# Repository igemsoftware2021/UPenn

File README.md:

# UPenn

OptoReader repository for software package to run the OptoReader, hardware files, and modeling scripts.

## Running the OptoReader

The OptoReader can be run using a computer and two Arduino Micros with the following provided code files: 

*OptoPlate_topArduino.ino* - Arduino code to control the stimulation plate. Takes in experiment stimulation settings, controls the 96 stimulation and optical density LEDs, and communicates with the reading plate for optical density measurements.

*PlateReader_bottomArduino.ino* - Arduino code to control the reading plate. Takes in experiment reading settings, controls the 96 excitation LEDs and photosensors, and communicates with the stimulation plate for optical density measurements. 

*OptoReader_Protocol.py* - Python code to take in inputs from the graphical user interface, keep track of experiment timing, and communicate with Arduinos to initiate readings and calibrate the optical density LEDs.

*GUI.py* - Python code creating a graphical user interface to take in user experiment inputs including stimulation settings, reading settings, feedback control, and experiment timing.

To run the OptoReader, first upload OptoPlate_topArduino.ino to the stimulation (top) plate Arduino and upload *PlateReader_bottomArduino.ino* to the reading (bottom) Arduino. Note the port name for each Arduino. If necessary, rename the port name from the preset COM11 and COM12 in *OptoReader_Protocol.py*. Finally, run GUI.py to open the graphical user interface and enter your experiment settings. Ensure that the image files *blue_logo.png* and *optologo_small.png* and the Python file *OptoReader_Protocol.py* are saved in the same folder as *GUI.py*.

## Hardware

### 3D Printed Parts
Includes files for our 3D-printed parts *Bottom_Adaptor.stl* and *Top_Adaptor.stl*. These files include the 3D model of the top adaptor and bottom adaptor, that fit each pcb board to a microwell plate.

### PCBs
Includes schematic files for our printed circuit boards (PCBs) *PlateReader.kicad_pcb* and *optoPlate96.kicad_pcb*. These can be sent directly to a company that provides printed circuit boards. The board components are soldered directly onto the boards. 

## Fluorescence Calibration Modeling

Files for our fluorescence calibration modeling include *FirstFit.m* and *Fluorescence_Calibration_Curve.m*. These files use our device’s fluorescence readings at different known concentrations to fit each well to a fluorescent calibration curve.

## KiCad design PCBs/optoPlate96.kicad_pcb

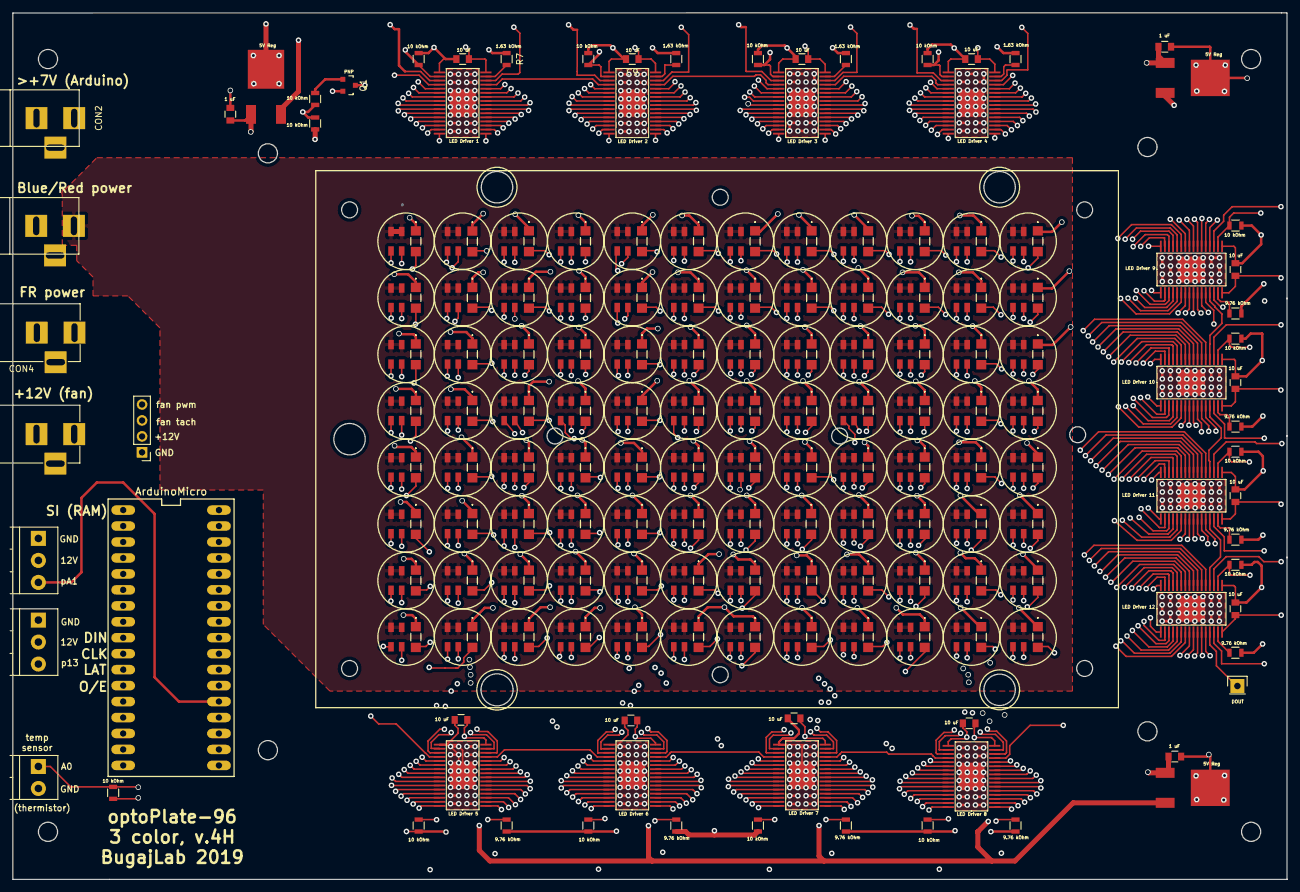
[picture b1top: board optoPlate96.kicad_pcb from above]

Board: 6 copper layers, 202.8 x 137.9 mm, 260 parts (0 on the bottom side), 332 nets.

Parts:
C7, C8, C9, C10, C11, C12, C13, C14, C15, C16, C17, C18, C19, C25, C27: C; C_0805
CON1, CON2, CON3, CON4: BARREL_JACK
D3, D5, D7, D9, D11, D13, D15, D17, D19, D21, D23, D25, D27, D29, D31, D33, D35, D37, D39, D41, D43, D45, D47, D49, D51, D53, D55, D57, D59, D61, D63, D65, D67, D69, D71, D73, D75, D77, D79, D81, D83, D85, D87, D89, D91, D93, D95, D97, D99, D101, D103, D105, D107, D109, D111, D113, D115, D117, D119, D121, D123, D125, D127, D129, D131, D133, D135, D137, D139, D141, D143, D145, D147, D149, D151, D153, D155, D157, D159, D161, D163, D165, D167, D169, D171, D173, D175, D177, D179, D181, D183, D185, D187, D189, D191, D193: LED; HSMCC380
D4, D6, D8, D10, D12, D14, D16, D18, D20, D22, D24, D26, D28, D30, D32, D34, D36, D38, D40, D42, D44, D46, D48, D50, D52, D54, D56, D58, D60, D62, D64, D66, D68, D70, D72, D74, D76, D78, D80, D82, D84, D86, D88, D90, D92, D94, D96, D98, D100, D102, D104, D106, D108, D110, D112, D114, D116, D118, D120, D122, D124, D126, D128, D130, D132, D134, D136, D138, D140, D142, D144, D146, D148, D150, D152, D154, D156, D158, D160, D162, D164, D166, D168, D170, D172, D174, D176, D178, D180, D182, D184, D186, D188, D190, D192, D194: BI_LED; BiLED3528RedBlue
P2: CONN_01X01; Pin_Header_Straight_1x01
P3, P6: CONN_01X03; TerminalBlock_Pheonix_PT-3.5mm_3pol
P4: CONN_01X04; Pin_Header_Straight_1x04_Pitch2.54mm
P5: CONN_01X02; TerminalBlock_Pheonix_PT-3.5mm_2pol
Q1: PNP; PNP_SOT-23_correct
R1, R2, R3, R6, R7, R8, R9, R10, R11, R12, R13, R14, R15, R16, R17, R18, R19, R20, R21, R22, R23, R24, R25, R26, R27, R28, R29: R; R_0805
U1: ArduinoMicro; ArduinoMicro_DIP34
U4, U17, U18: LM2931AZ-5.0; Voltage_Regulator_LM2931ADT-5.0_noHoles
U5, U6, U7, U8, U9, U10, U11, U12, U13, U14, U15, U16: TLC5947; TLC5947_noHoles

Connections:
/3.3V: CON1.1, D4.1, D4.2, D6.1, D6.2, D8.1, D8.2, D10.1, D10.2, D12.1, D12.2, D14.1, D14.2, D16.1, D16.2, D18.1, D18.2, D20.1, D20.2, D22.1, D22.2, D24.1, D24.2, D26.1, D26.2, D28.1, D28.2, D30.1, D30.2, D32.1, D32.2, D34.1, D34.2, D36.1, D36.2, D38.1, D38.2, D40.1, D40.2, D42.1, D42.2, D44.1, D44.2, D46.1, D46.2, D48.1, D48.2, D50.1, D50.2, D52.1, D52.2, D54.1, D54.2, D56.1, D56.2, D58.1, D58.2, D60.1, D60.2, D62.1, D62.2, D64.1, D64.2, D66.1, D66.2, D68.1, D68.2, D70.1, D70.2, D72.1, D72.2, D74.1, D74.2, D76.1, D76.2, D78.1, D78.2, D80.1, D80.2, D82.1, D82.2, D84.1, D84.2, D86.1, D86.2, D88.1, D88.2, D90.1, D90.2, D92.1, D92.2, D94.1, D94.2, D96.1, D96.2, D98.1, D98.2, D100.1, D100.2, D102.1, D102.2, D104.1, D104.2, D106.1, D106.2, D108.1, D108.2, D110.1, D110.2, D112.1, D112.2, D114.1, D114.2, D116.1, D116.2, D118.1, D118.2, D120.1, D120.2, D122.1, D122.2, D124.1, D124.2, D126.1, D126.2, D128.1, D128.2, D130.1, D130.2, D132.1, D132.2, D134.1, D134.2, D136.1, D136.2, D138.1, D138.2, D140.1, D140.2, D142.1, D142.2, D144.1, D144.2, D146.1, D146.2, D148.1, D148.2, D150.1, D150.2, D152.1, D152.2, D154.1, D154.2, D156.1, D156.2, D158.1, D158.2, D160.1, D160.2, D162.1, D162.2, D164.1, D164.2, D166.1, D166.2, D168.1, D168.2, D170.1, D170.2, D172.1, D172.2, D174.1, D174.2, D176.1, D176.2, D178.1, D178.2, D180.1, D180.2, D182.1, D182.2, D184.1, D184.2, D186.1, D186.2, D188.1, D188.2, D190.1, D190.2, D192.1, D192.2, D194.1, D194.2
/3.3Vreal: R3.2, U1.19, U1.20
/5V: C13.1, C25.1, C27.1, CON2.1, U1.32, U4.3, U17.3, U18.3
/+12V: CON3.1, P3.2, P4.2, P6.2
/B1: D4.4, U5.5
/B2: D6.4, U5.6
/B3: D8.4, U5.7
/B4: D10.4, U5.8
/B5: D12.4, U5.9
/B6: D14.4, U5.10
/B7: D16.4, U5.11
/B8: D18.4, U5.12
/B9: D20.4, U5.13
/B10: D22.4, U5.14
/B11: D24.4, U5.15
/B12: D26.4, U5.16
/B13: D28.4, U5.17
/B14: D30.4, U5.18
/B15: D32.4, U5.19
/B16: D34.4, U5.20
/B17: D36.4, U5.21
/B18: D38.4, U5.22
/B19: D40.4, U5.23
/B20: D42.4, U5.24
/B21: D44.4, U5.25
/B22: D46.4, U5.26
/B23: D48.4, U5.27
/B24: D50.4, U5.28
/B25: D52.4, U6.5
/B26: D54.4, U6.6
/B27: D56.4, U6.7
/B28: D58.4, U6.8
/B29: D60.4, U6.9
/B30: D62.4, U6.10
/B31: D64.4, U6.11
/B32: D66.4, U6.12
/B33: D68.4, U6.13
/B34: D70.4, U6.14
/B35: D72.4, U6.15
/B36: D74.4, U6.16
/B37: D76.4, U6.17
/B38: D78.4, U6.18
/B39: D80.4, U6.19
/B40: D82.4, U6.20
/B41: D84.4, U6.21
/B42: D86.4, U6.22
/B43: D88.4, U6.23
/B44: D90.4, U6.24
/B45: D92.4, U6.25
/B46: D94.4, U6.26
/B47: D96.4, U6.27
/B48: D98.4, U6.28
/B49: D100.4, U7.5
/B50: D102.4, U7.6
/B51: D104.4, U7.7
/B52: D106.4, U7.8
/B53: D108.4, U7.9
/B54: D110.4, U7.10
/B55: D112.4, U7.11
/B56: D114.4, U7.12
/B57: D116.4, U7.13
/B58: D118.4, U7.14
/B59: D120.4, U7.15
/B60: D122.4, U7.16
/B61: D124.4, U7.17
/B62: D126.4, U7.18
/B63: D128.4, U7.19
/B64: D130.4, U7.20
/B65: D132.4, U7.21
/B66: D134.4, U7.22
/B67: D136.4, U7.23
/B68: D138.4, U7.24
/B69: D140.4, U7.25
/B70: D142.4, U7.26
/B71: D144.4, U7.27
/B72: D146.4, U7.28
/B73: D148.4, U8.5
/B74: D150.4, U8.6
/B75: D152.4, U8.7
/B76: D154.4, U8.8
/B77: D156.4, U8.9
/B78: D158.4, U8.10
/B79: D160.4, U8.11
/B80: D162.4, U8.12
/B81: D164.4, U8.13
/B82: D166.4, U8.14
/B83: D168.4, U8.15
/B84: D170.4, U8.16
/B85: D172.4, U8.17
/B86: D174.4, U8.18
/B87: D176.4, U8.19
/B88: D178.4, U8.20
/B89: D180.4, U8.21
/B90: D182.4, U8.22
/B91: D184.4, U8.23
/B92: D186.4, U8.24
/B93: D188.4, U8.25
/B94: D190.4, U8.26
/B95: D192.4, U8.27
/B96: D194.4, U8.28
/BLANK: Q1.3, R6.2, R8.2, R10.2, R12.2, R14.2, R16.2, R18.2, R20.2, R22.2, R24.2, R26.2, R28.2, U5.2, U6.2, U7.2, U8.2, U9.2, U10.2, U11.2, U12.2, U13.2, U14.2, U15.2, U16.2
/CLK: U1.10, U5.3, U6.3, U7.3, U8.3, U9.3, U10.3, U11.3, U12.3, U13.3, U14.3, U15.3, U16.3
/DIN: U1.9, U5.4
/DOUT: P2.1, U16.29
/FR1: D3.2, U13.5
/FR2: D5.2, U13.17
/FR3: D7.2, U14.5
/FR4: D9.2, U14.17
/FR5: D11.2, U15.5
/FR6: D13.2, U15.17
/FR7: D15.2, U16.5
/FR8: D17.2, U16.17
/FR9: D19.2, U13.6
/FR10: D21.2, U13.18
/FR11: D23.2, U14.6
/FR12: D25.2, U14.18
/FR13: D27.2, U15.6
/FR14: D29.2, U15.18
/FR15: D31.2, U16.6
/FR16: D33.2, U16.18
/FR17: D35.2, U13.7
/FR18: D37.2, U13.19
/FR19: D39.2, U14.7
/FR20: D41.2, U14.19
/FR21: D43.2, U15.7
/FR22: D45.2, U15.19
/FR23: D47.2, U16.7
/FR24: D49.2, U16.19
/FR25: D51.2, U13.8
/FR26: D53.2, U13.20
/FR27: D55.2, U14.8
/FR28: D57.2, U14.20
/FR29: D59.2, U15.8
/FR30: D61.2, U15.20
/FR31: D63.2, U16.8
/FR32: D65.2, U16.20
/FR33: D67.2, U13.9
/FR34: D69.2, U13.21
/FR35: D71.2, U14.9
/FR36: D73.2, U14.21
/FR37: D75.2, U15.9
/FR38: D77.2, U15.21
/FR39: D79.2, U16.9
/FR40: D81.2, U16.21
/FR41: D83.2, U13.10
/FR42: D85.2, U13.22
/FR43: D87.2, U14.10
/FR44: D89.2, U14.22
/FR45: D91.2, U15.10
/FR46: D93.2, U15.22
/FR47: D95.2, U16.10
/FR48: D97.2, U16.22
/FR49: D99.2, U13.11
/FR50: D101.2, U13.23
/FR51: D103.2, U14.11
/FR52: D105.2, U14.23
/FR53: D107.2, U15.11
/FR54: D109.2, U15.23
/FR55: D111.2, U16.11
/FR56: D113.2, U16.23
/FR57: D115.2, U13.12
/FR58: D117.2, U13.24
/FR59: D119.2, U14.12
/FR60: D121.2, U14.24
/FR61: D123.2, U15.12
/FR62: D125.2, U15.24
/FR63: D127.2, U16.12
/FR64: D129.2, U16.24
/FR65: D131.2, U13.13
/FR66: D133.2, U13.25
/FR67: D135.2, U14.13
/FR68: D137.2, U14.25
/FR69: D139.2, U15.13
/FR70: D141.2, U15.25
/FR71: D143.2, U16.13
/FR72: D145.2, U16.25
/FR73: D147.2, U13.14
/FR74: D149.2, U13.26
/FR75: D151.2, U14.14
/FR76: D153.2, U14.26
/FR77: D155.2, U15.14
/FR78: D157.2, U15.26
/FR79: D159.2, U16.14
/FR80: D161.2, U16.26
/FR81: D163.2, U13.15
/FR82: D165.2, U13.27
/FR83: D167.2, U14.15
/FR84: D169.2, U14.27
/FR85: D171.2, U15.15
/FR86: D173.2, U15.27
/FR87: D175.2, U16.15
/FR88: D177.2, U16.27
/FR89: D179.2, U13.16
/FR90: D181.2, U13.28
/FR91: D183.2, U14.16
/FR92: D185.2, U14.28
/FR93: D187.2, U15.16
/FR94: D189.2, U15.28
/FR95: D191.2, U16.16
/FR96: D193.2, U16.28
/LAT: U1.11, U5.30, U6.30, U7.30, U8.30, U9.30, U10.30, U11.30, U12.30, U13.30, U14.30, U15.30, U16.30
/R1: D4.3, U9.5
/R2: D6.3, U9.6
/R3: D8.3, U9.7
/R4: D10.3, U9.8
/R5: D12.3, U9.9
/R6: D14.3, U9.10
/R7: D16.3, U9.11
/R8: D18.3, U9.12
/R9: D20.3, U9.13
/R10: D22.3, U9.14
/R11: D24.3, U9.15
/R12: D26.3, U9.16
/R13: D28.3, U9.17
/R14: D30.3, U9.18
/R15: D32.3, U9.19
/R16: D34.3, U9.20
/R17: D36.3, U9.21
/R18: D38.3, U9.22
/R19: D40.3, U9.23
/R20: D42.3, U9.24
/R21: D44.3, U9.25
/R22: D46.3, U9.26
/R23: D48.3, U9.27
/R24: D50.3, U9.28
/R25: D52.3, U10.5
/R26: D54.3, U10.6
/R27: D56.3, U10.7
/R28: D58.3, U10.8
/R29: D60.3, U10.9
/R30: D62.3, U10.10
/R31: D64.3, U10.11
/R32: D66.3, U10.12
/R33: D68.3, U10.13
/R34: D70.3, U10.14
/R35: D72.3, U10.15
/R36: D74.3, U10.16
/R37: D76.3, U10.17
/R38: D78.3, U10.18
/R39: D80.3, U10.19
/R40: D82.3, U10.20
/R41: D84.3, U10.21
/R42: D86.3, U10.22
/R43: D88.3, U10.23
/R44: D90.3, U10.24
/R45: D92.3, U10.25
/R46: D94.3, U10.26
/R47: D96.3, U10.27
/R48: D98.3, U10.28
/R49: D100.3, U11.5
/R50: D102.3, U11.6
/R51: D104.3, U11.7
/R52: D106.3, U11.8
/R53: D108.3, U11.9
/R54: D110.3, U11.10
/R55: D112.3, U11.11
/R56: D114.3, U11.12
/R57: D116.3, U11.13
/R58: D118.3, U11.14
/R59: D120.3, U11.15
/R60: D122.3, U11.16
/R61: D124.3, U11.17
/R62: D126.3, U11.18
/R63: D128.3, U11.19
/R64: D130.3, U11.20
/R65: D132.3, U11.21
/R66: D134.3, U11.22
/R67: D136.3, U11.23
/R68: D138.3, U11.24
/R69: D140.3, U11.25
/R70: D142.3, U11.26
/R71: D144.3, U11.27
/R72: D146.3, U11.28
/R73: D148.3, U12.5
/R74: D150.3, U12.6
/R75: D152.3, U12.7
/R76: D154.3, U12.8
/R77: D156.3, U12.9
/R78: D158.3, U12.10
/R79: D160.3, U12.11
/R80: D162.3, U12.12
/R81: D164.3, U12.13
/R82: D166.3, U12.14
/R83: D168.3, U12.15
/R84: D170.3, U12.16
/R85: D172.3, U12.17
/R86: D174.3, U12.18
/R87: D176.3, U12.19
/R88: D178.3, U12.20
/R89: D180.3, U12.21
/R90: D182.3, U12.22
/R91: D184.3, U12.23
/R92: D186.3, U12.24
/R93: D188.3, U12.25
/R94: D190.3, U12.26
/R95: D192.3, U12.27
/R96: D194.3, U12.28
/Vfr: CON4.1, D3.1, D5.1, D7.1, D9.1, D11.1, D13.1, D15.1, D17.1, D19.1, D21.1, D23.1, D25.1, D27.1, D29.1, D31.1, D33.1, D35.1, D37.1, D39.1, D41.1, D43.1, D45.1, D47.1, D49.1, D51.1, D53.1, D55.1, D57.1, D59.1, D61.1, D63.1, D65.1, D67.1, D69.1, D71.1, D73.1, D75.1, D77.1, D79.1, D81.1, D83.1, D85.1, D87.1, D89.1, D91.1, D93.1, D95.1, D97.1, D99.1, D101.1, D103.1, D105.1, D107.1, D109.1, D111.1, D113.1, D115.1, D117.1, D119.1, D121.1, D123.1, D125.1, D127.1, D129.1, D131.1, D133.1, D135.1, D137.1, D139.1, D141.1, D143.1, D145.1, D147.1, D149.1, D151.1, D153.1, D155.1, D157.1, D159.1, D161.1, D163.1, D165.1, D167.1, D169.1, D171.1, D173.1, D175.1, D177.1, D179.1, D181.1, D183.1, D185.1, D187.1, D189.1, D191.1, D193.1
/aux_pwm1: P3.3, U1.18
/aux_pwm2: P6.3, U1.22
/fan_pwm: P4.4, U1.16
/fan_sense: P4.3, U1.15
/tempSense: P5.1, R3.1, U1.21
GND: C7.2, C8.2, C9.2, C10.2, C11.2, C12.2, C13.2, C14.2, C15.2, C16.2, C17.2, C18.2, C19.2, C25.2, C27.2, CON1.2, CON1.3, CON2.2, CON2.3, CON3.2, CON3.3, CON4.2, CON4.3, P3.1, P4.1, P5.2, P6.1, R1.1, R6.1, R7.1, R8.1, R9.1, R10.1, R11.1, R12.1, R13.1, R14.1, R15.1, R16.1, R17.1, R18.1, R19.1, R20.1, R21.1, R22.1, R23.1, R24.1, R25.1, R26.1, R27.1, R28.1, R29.1, U1.6, U1.31, U4.2, U5.1, U6.1, U7.1, U8.1, U9.1, U10.1, U11.1, U12.1, U13.1, U14.1, U15.1, U16.1, U17.2, U18.2
unnamed: C7.1, C10.1, C15.1, C16.1, U9.32, U10.32, U11.32, U12.32, U18.1
unnamed: C8.1, C9.1, C11.1, C12.1, Q1.1, U4.1, U5.32, U6.32, U7.32, U8.32
unnamed: C14.1, C17.1, C18.1, C19.1, U13.32, U14.32, U15.32, U16.32, U17.1
unnamed: Q1.2, R2.2
unnamed: R1.2, R2.1, U1.12
unnamed: R7.2, U5.31
unnamed: R9.2, U6.31
unnamed: R11.2, U7.31
unnamed: R13.2, U8.31
unnamed: R15.2, U9.31
unnamed: R17.2, U10.31
unnamed: R19.2, U11.31
unnamed: R21.2, U12.31
unnamed: R23.2, U13.31
unnamed: R25.2, U14.31
unnamed: R27.2, U15.31
unnamed: R29.2, U16.31
unnamed: U5.29, U6.4
unnamed: U6.29, U7.4
unnamed: U7.29, U8.4
unnamed: U8.29, U9.4
unnamed: U9.29, U10.4
unnamed: U10.29, U11.4
unnamed: U11.29, U12.4
unnamed: U12.29, U13.4
unnamed: U13.29, U14.4
unnamed: U14.29, U15.4
unnamed: U15.29, U16.4

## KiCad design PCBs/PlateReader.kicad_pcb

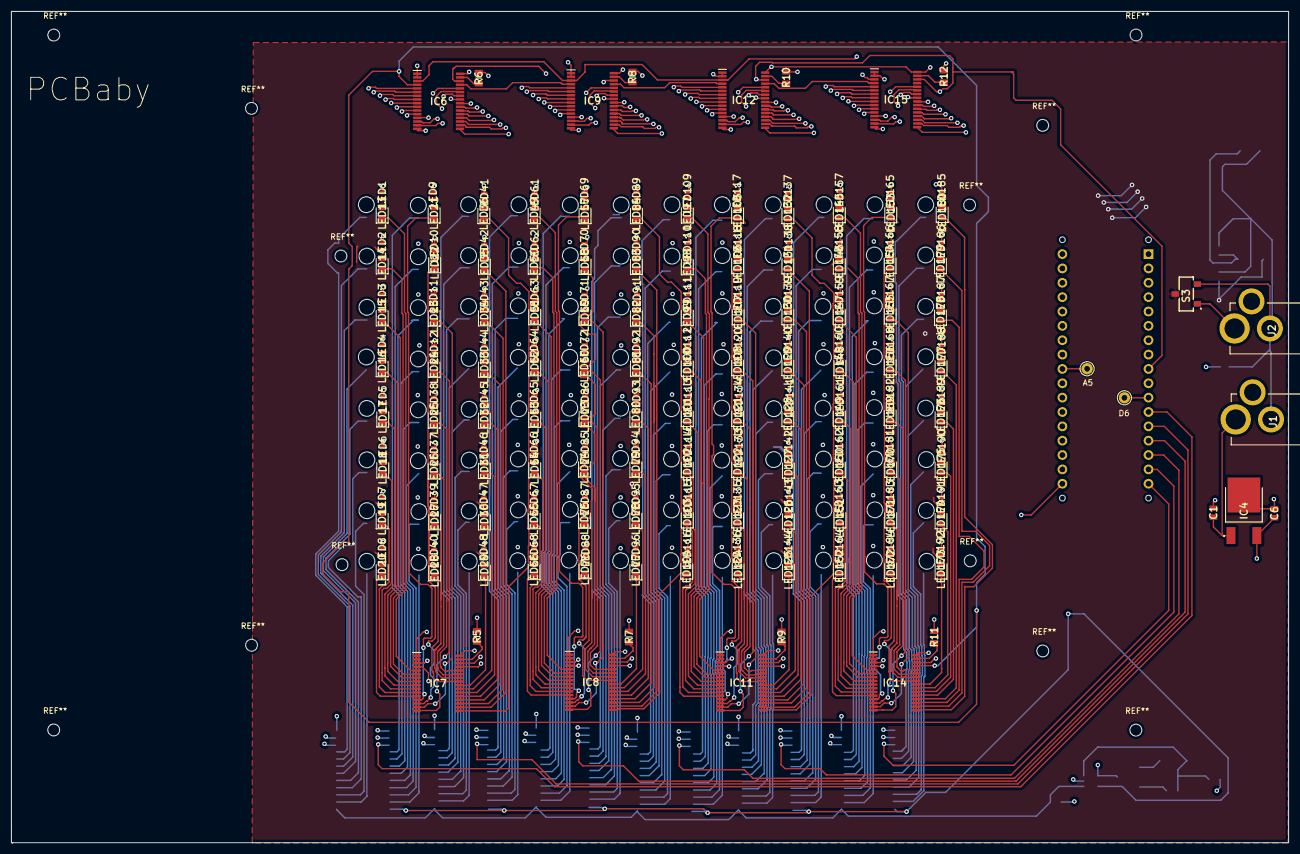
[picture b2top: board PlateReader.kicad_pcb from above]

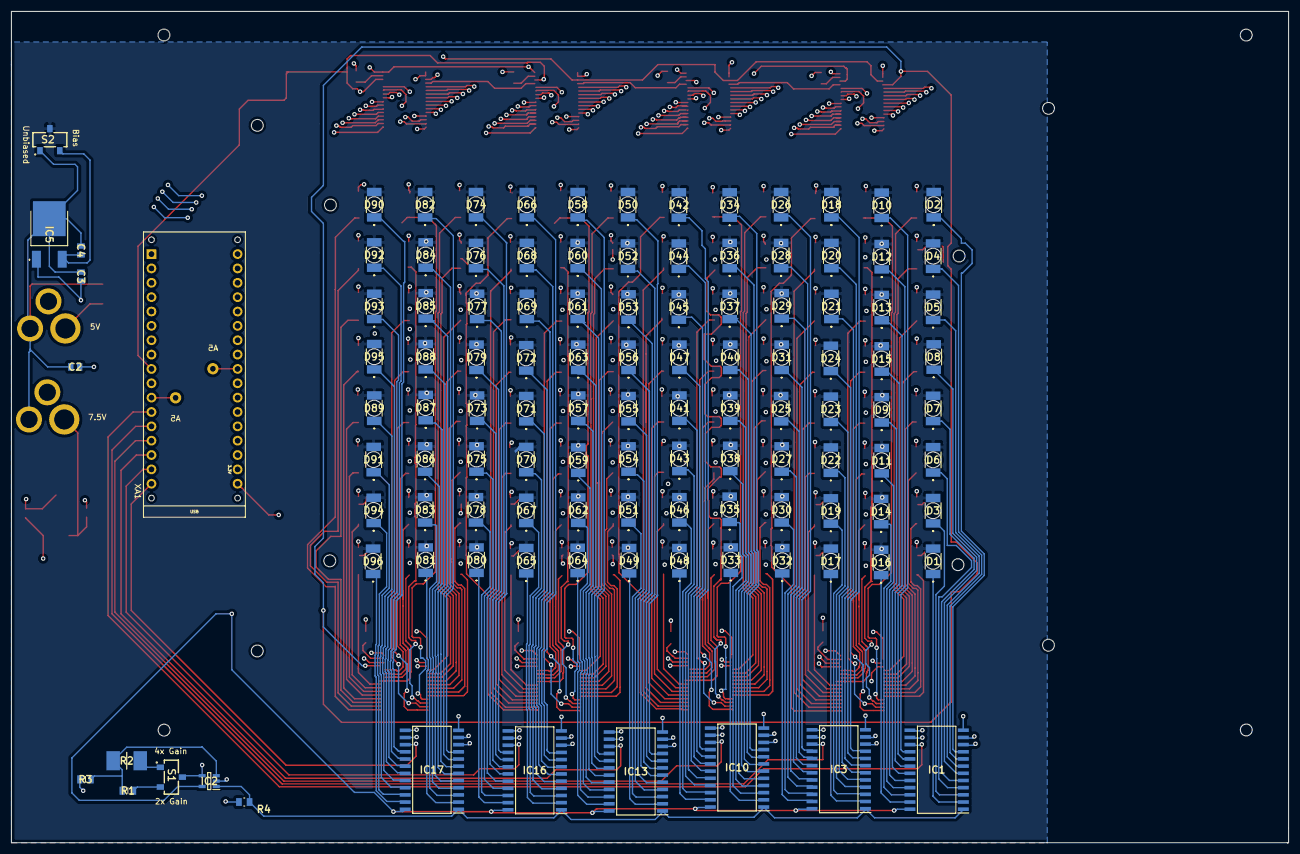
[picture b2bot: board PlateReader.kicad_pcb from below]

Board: 4 copper layers, 226.0 x 147.1 mm, 330 parts (114 on the bottom side), 328 nets.

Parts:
A5, A5#2: Pin_D1.0mm_L10.0mm
C1, C2, C3, C4: UMK212B7105KG-T; CAPC2012X135N
C6: GMK212BBJ106KG-T; CAPC2012X135N
D1, D2, D3, D4, D5, D6, D7, D8, D9, D10, D11, D12, D13, D14, D15, D16, D17, D18, D19, D20, D21, D22, D23, D24, D25, D26, D27, D28, D29, D30, D31, D32, D33, D34, D35, D36, D37, D38, D39, D40, D41, D42, D43, D44, D45, D46, D47, D48, D49, D50, D51, D52, D53, D54, D55, D56, D57, D58, D59, D60, D61, D62, D63, D64, D65, D66, D67, D68, D69, D70, D71, D72, D73, D74, D75, D76, D77, D78, D79, D80, D81, D82, D83, D84, D85, D86, D87, D88, D89, D90, D91, D92, D93, D94, D95, D96: SFH_2270R; SFH2270R
IC1, IC3, IC10, IC13, IC16, IC17: CD74HCT4067M; SOIC127P1030X265-24N
IC2: NCV321SN3T1G; SOT95P275X110-5N
IC4, IC5: NCP5501DT15RKG; NCP5501DT50RKG
IC6, IC7, IC8, IC9, IC11, IC12, IC14, IC15: TLC5947DAP; SOP65P810X120-33N
J1, J2: RAPC722X
LED1, LED2, LED3, LED4, LED5, LED6, LED7, LED8, LED9, LED10, LED11, LED12, LED37, LED38, LED39, LED40, LED41, LED42, LED43, LED44, LED45, LED46, LED47, LED48, LED61, LED62, LED63, LED64, LED65, LED66, LED67, LED68, LED69, LED70, LED71, LED72, LED85, LED86, LED87, LED88, LED89, LED90, LED91, LED92, LED93, LED94, LED95, LED96, LED109, LED110, LED111, LED112, LED113, LED114, LED115, LED116, LED117, LED118, LED119, LED120, LED133, LED134, LED135, LED136, LED137, LED138, LED139, LED140, LED141, LED142, LED143, LED144, LED157, LED158, LED159, LED160, LED161, LED162, LED163, LED164, LED165, LED166, LED167, LED168, LED181, LED182, LED183, LED184, LED185, LED186, LED187, LED188, LED189, LED190, LED191, LED192: ATS2012UV395
LED13, LED14, LED15, LED16, LED17, LED18, LED19, LED20, LED21, LED22, LED23, LED24, LED25, LED26, LED27, LED28, LED29, LED30, LED31, LED32, LED33, LED34, LED35, LED36, LED49, LED50, LED51, LED52, LED53, LED54, LED55, LED56, LED57, LED58, LED59, LED60, LED73, LED74, LED75, LED76, LED77, LED78, LED79, LED80, LED81, LED82, LED83, LED84, LED97, LED98, LED99, LED100, LED101, LED102, LED103, LED104, LED105, LED106, LED107, LED108, LED121, LED122, LED123, LED124, LED125, LED126, LED127, LED128, LED129, LED130, LED131, LED132, LED145, LED146, LED147, LED148, LED149, LED150, LED151, LED152, LED153, LED154, LED155, LED156, LED169, LED170, LED171, LED172, LED173, LED174, LED175, LED176, LED177, LED178, LED179, LED180: 155060BS75300; LEDC2012X85N
R1, R3: RC0805JR-07130RL; RESC2012X60N
R2: CRGH2512J390R; RESC6432X65N
R4: CRCW080550M0JPEAHR; RESC2013X65N
R5, R6, R7, R8, R9, R10, R11, R12: RN732ATTD1651B25; RESC2012X60N
S1, S2, S3: CJS-1200TB; B-TYPE
XA1: Arduino_Micro_Socket

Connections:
+5V: C3.2, IC5.1, LED1.2, LED2.2, LED3.2, LED4.2, LED5.2, LED6.2, LED7.2, LED8.2, LED9.2, LED10.2, LED11.2, LED12.2, LED13.2, LED14.2, LED15.2, LED16.2, LED17.2, LED18.2, LED19.2, LED20.2, LED21.2, LED22.2, LED23.2, LED24.2, LED25.2, LED26.2, LED27.2, LED28.2, LED29.2, LED30.2, LED31.2, LED32.2, LED33.2, LED34.2, LED35.2, LED36.2, LED37.2, LED38.2, LED39.2, LED40.2, LED41.2, LED42.2, LED43.2, LED44.2, LED45.2, LED46.2, LED47.2, LED48.2, LED49.2, LED50.2, LED51.2, LED52.2, LED53.2, LED54.2, LED55.2, LED56.2, LED57.2, LED58.2, LED59.2, LED60.2, LED61.2, LED62.2, LED63.2, LED64.2, LED65.2, LED66.2, LED67.2, LED68.2, LED69.2, LED70.2, LED71.2, LED72.2, LED73.2, LED74.2, LED75.2, LED76.2, LED77.2, LED78.2, LED79.2, LED80.2, LED81.2, LED82.2, LED83.2, LED84.2, LED85.2, LED86.2, LED87.2, LED88.2, LED89.2, LED90.2, LED91.2, LED92.2, LED93.2, LED94.2, LED95.2, LED96.2, LED97.2, LED98.2, LED99.2, LED100.2, LED101.2, LED102.2, LED103.2, LED104.2, LED105.2, LED106.2, LED107.2, LED108.2, LED109.2, LED110.2, LED111.2, LED112.2, LED113.2, LED114.2, LED115.2, LED116.2, LED117.2, LED118.2, LED119.2, LED120.2, LED121.2, LED122.2, LED123.2, LED124.2, LED125.2, LED126.2, LED127.2, LED128.2, LED129.2, LED130.2, LED131.2, LED132.2, LED133.2, LED134.2, LED135.2, LED136.2, LED137.2, LED138.2, LED139.2, LED140.2, LED141.2, LED142.2, LED143.2, LED144.2, LED145.2, LED146.2, LED147.2, LED148.2, LED149.2, LED150.2, LED151.2, LED152.2, LED153.2, LED154.2, LED155.2, LED156.2, LED157.2, LED158.2, LED159.2, LED160.2, LED161.2, LED162.2, LED163.2, LED164.2, LED165.2, LED166.2, LED167.2, LED168.2, LED169.2, LED170.2, LED171.2, LED172.2, LED173.2, LED174.2, LED175.2, LED176.2, LED177.2, LED178.2, LED179.2, LED180.2, LED181.2, LED182.2, LED183.2, LED184.2, LED185.2, LED186.2, LED187.2, LED188.2, LED189.2, LED190.2, LED191.2, LED192.2, S3.2
+7.5V: C1.2, IC4.1, J1.3
GND: C1.1, C2.1, C3.1, C4.1, C6.1, IC1.12, IC2.2, IC3.12, IC4.2, IC5.2, IC6.1, IC6.2, IC7.1, IC7.2, IC8.1, IC8.2, IC9.1, IC9.2, IC10.12, IC11.1, IC11.2, IC12.1, IC12.2, IC13.12, IC14.1, IC14.2, IC15.1, IC15.2, IC16.12, IC17.12, J1.2, J2.2, R3.2, R4.2, R5.1, R6.1, R7.1, R8.1, R9.1, R10.1, R11.1, R12.1, S2.1, S3.3, XA1.GND1
unnamed: C2.2, C6.2, IC1.24, IC2.5, IC3.24, IC4.3, IC6.32, IC7.32, IC8.32, IC9.32, IC10.24, IC11.32, IC12.32, IC13.24, IC14.32, IC15.32, IC16.24, IC17.24
unnamed: C4.2, IC5.3, S2.3
unnamed: D1.1, IC1.2
unnamed: D1.2, D2.2, D3.2, D4.2, D5.2, D6.2, D7.2, D8.2, D9.2, D10.2, D11.2, D12.2, D13.2, D14.2, D15.2, D16.2, D17.2, D18.2, D19.2, D20.2, D21.2, D22.2, D23.2, D24.2, D25.2, D26.2, D27.2, D28.2, D29.2, D30.2, D31.2, D32.2, D33.2, D34.2, D35.2, D36.2, D37.2, D38.2, D39.2, D40.2, D41.2, D42.2, D43.2, D44.2, D45.2, D46.2, D47.2, D48.2, D49.2, D50.2, D51.2, D52.2, D53.2, D54.2, D55.2, D56.2, D57.2, D58.2, D59.2, D60.2, D61.2, D62.2, D63.2, D64.2, D65.2, D66.2, D67.2, D68.2, D69.2, D70.2, D71.2, D72.2, D73.2, D74.2, D75.2, D76.2, D77.2, D78.2, D79.2, D80.2, D81.2, D82.2, D83.2, D84.2, D85.2, D86.2, D87.2, D88.2, D89.2, D90.2, D91.2, D92.2, D93.2, D94.2, D95.2, D96.2, S2.2
unnamed: D2.1, IC1.9
unnamed: D3.1, IC1.3
unnamed: D4.1, IC1.8
unnamed: D5.1, IC1.7
unnamed: D6.1, IC1.4
unnamed: D7.1, IC1.5
unnamed: D8.1, IC1.6
unnamed: D9.1, IC1.20
unnamed: D10.1, IC1.16
unnamed: D11.1, IC1.21
unnamed: D12.1, IC1.17
unnamed: D13.1, IC1.18
unnamed: D14.1, IC1.22
unnamed: D15.1, IC1.19
unnamed: D16.1, IC1.23
unnamed: D17.1, IC3.2
unnamed: D18.1, IC3.9
unnamed: D19.1, IC3.3
unnamed: D20.1, IC3.8
unnamed: D21.1, IC3.7
unnamed: D22.1, IC3.4
unnamed: D23.1, IC3.5
unnamed: D24.1, IC3.6
unnamed: D25.1, IC3.20
unnamed: D26.1, IC3.16
unnamed: D27.1, IC3.21
unnamed: D28.1, IC3.17
unnamed: D29.1, IC3.18
unnamed: D30.1, IC3.22
unnamed: D31.1, IC3.19
unnamed: D32.1, IC3.23
unnamed: D33.1, IC10.2
unnamed: D34.1, IC10.9
unnamed: D35.1, IC10.3
unnamed: D36.1, IC10.8
unnamed: D37.1, IC10.7
unnamed: D38.1, IC10.4
unnamed: D39.1, IC10.5
unnamed: D40.1, IC10.6
unnamed: D41.1, IC10.20
unnamed: D42.1, IC10.16
unnamed: D43.1, IC10.21
unnamed: D44.1, IC10.17
unnamed: D45.1, IC10.18
unnamed: D46.1, IC10.22
unnamed: D47.1, IC10.19
unnamed: D48.1, IC10.23
unnamed: D49.1, IC13.2
unnamed: D50.1, IC13.9
unnamed: D51.1, IC13.3
unnamed: D52.1, IC13.8
unnamed: D53.1, IC13.7
unnamed: D54.1, IC13.4
unnamed: D55.1, IC13.5
unnamed: D56.1, IC13.6
unnamed: D57.1, IC13.20
unnamed: D58.1, IC13.16
unnamed: D59.1, IC13.21
unnamed: D60.1, IC13.17
unnamed: D61.1, IC13.18
unnamed: D62.1, IC13.22
unnamed: D63.1, IC13.19
unnamed: D64.1, IC13.23
unnamed: D65.1, IC16.2
unnamed: D66.1, IC16.9
unnamed: D67.1, IC16.3
unnamed: D68.1, IC16.8
unnamed: D69.1, IC16.7
unnamed: D70.1, IC16.4
unnamed: D71.1, IC16.5
unnamed: D72.1, IC16.6
unnamed: D73.1, IC16.20
unnamed: D74.1, IC16.16
unnamed: D75.1, IC16.21
unnamed: D76.1, IC16.17
unnamed: D77.1, IC16.18
unnamed: D78.1, IC16.22
unnamed: D79.1, IC16.19
unnamed: D80.1, IC16.23
unnamed: D81.1, IC17.2
unnamed: D82.1, IC17.9
unnamed: D83.1, IC17.3
unnamed: D84.1, IC17.8
unnamed: D85.1, IC17.7
unnamed: D86.1, IC17.4
unnamed: D87.1, IC17.5
unnamed: D88.1, IC17.6
unnamed: D89.1, IC17.20
unnamed: D90.1, IC17.16
unnamed: D91.1, IC17.21
unnamed: D92.1, IC17.17
unnamed: D93.1, IC17.18
unnamed: D94.1, IC17.22
unnamed: D95.1, IC17.19
unnamed: D96.1, IC17.23
unnamed: IC1.1, IC2.1, IC3.1, IC10.1, IC13.1, IC16.1, IC17.1, R4.1
unnamed: IC1.10, IC3.10, IC10.10, IC13.10, IC16.10, IC17.10, XA1.A1
unnamed: IC1.11, IC3.11, IC10.11, IC13.11, IC16.11, IC17.11, XA1.A2
unnamed: IC1.13, IC3.13, IC10.13, IC13.13, IC16.13, IC17.13, XA1.A4
unnamed: IC1.14, IC3.14, IC10.14, IC13.14, IC16.14, IC17.14, XA1.A3
unnamed: IC1.15, XA1.D7
unnamed: IC2.3, R1.2, R2.2, R3.1
unnamed: IC2.4, S1.2, XA1.A0
unnamed: IC3.15, XA1.D8
unnamed: IC6.5, LED1.1
unnamed: IC6.6, LED2.1
unnamed: IC6.7, LED3.1
unnamed: IC6.8, LED4.1
unnamed: IC6.9, LED5.1
unnamed: IC6.10, LED6.1
unnamed: IC6.11, LED7.1
unnamed: IC6.12, LED8.1
unnamed: IC6.13, LED9.1
unnamed: IC6.14, LED10.1
unnamed: IC6.15, LED11.1
unnamed: IC6.16, LED12.1
unnamed: IC6.17, LED48.1
unnamed: IC6.18, LED47.1
unnamed: IC6.19, LED46.1
unnamed: IC6.20, LED45.1
unnamed: IC6.21, LED44.1
unnamed: IC6.22, LED43.1
unnamed: IC6.23, LED42.1
unnamed: IC6.24, LED41.1
unnamed: IC6.25, LED40.1
unnamed: IC6.26, LED39.1
unnamed: IC6.27, LED38.1
unnamed: IC6.28, LED37.1
unnamed: IC6.29, IC9.4
unnamed: IC6.31, R6.2
unnamed: IC7.4, XA1.D13
unnamed: IC7.5, LED13.1
unnamed: IC7.6, LED14.1
unnamed: IC7.7, LED15.1
unnamed: IC7.8, LED16.1
unnamed: IC7.9, LED17.1
unnamed: IC7.10, LED18.1
unnamed: IC7.11, LED19.1
unnamed: IC7.12, LED20.1
unnamed: IC7.13, LED21.1
unnamed: IC7.14, LED22.1
unnamed: IC7.15, LED23.1
unnamed: IC7.16, LED24.1
unnamed: IC7.17, LED36.1
unnamed: IC7.18, LED35.1
unnamed: IC7.19, LED34.1
unnamed: IC7.20, LED33.1
unnamed: IC7.21, LED32.1
unnamed: IC7.22, LED31.1
unnamed: IC7.23, LED30.1
unnamed: IC7.24, LED29.1
unnamed: IC7.25, LED28.1
unnamed: IC7.26, LED27.1
unnamed: IC7.27, LED26.1
unnamed: IC7.28, LED25.1
unnamed: IC7.29, IC8.4
unnamed: IC7.31, R5.2
unnamed: IC8.5, LED49.1
unnamed: IC8.6, LED50.1
unnamed: IC8.7, LED51.1
unnamed: IC8.8, LED52.1
unnamed: IC8.9, LED53.1
unnamed: IC8.10, LED54.1
unnamed: IC8.11, LED55.1
unnamed: IC8.12, LED56.1
unnamed: IC8.13, LED57.1
unnamed: IC8.14, LED58.1
unnamed: IC8.15, LED59.1
unnamed: IC8.16, LED60.1
unnamed: IC8.17, LED84.1
unnamed: IC8.18, LED83.1
unnamed: IC8.19, LED82.1
unnamed: IC8.20, LED81.1
unnamed: IC8.21, LED80.1
unnamed: IC8.22, LED79.1
unnamed: IC8.23, LED78.1
unnamed: IC8.24, LED77.1
unnamed: IC8.25, LED76.1
unnamed: IC8.26, LED75.1
unnamed: IC8.27, LED74.1
unnamed: IC8.28, LED73.1
unnamed: IC8.31, R7.2
unnamed: IC9.5, LED61.1
unnamed: IC9.6, LED62.1
unnamed: IC9.7, LED63.1
unnamed: IC9.8, LED64.1
unnamed: IC9.9, LED65.1
unnamed: IC9.10, LED66.1
unnamed: IC9.11, LED67.1
unnamed: IC9.12, LED68.1
unnamed: IC9.13, LED69.1
unnamed: IC9.14, LED70.1
unnamed: IC9.15, LED71.1
unnamed: IC9.16, LED72.1
unnamed: IC9.17, LED96.1
unnamed: IC9.18, LED95.1
unnamed: IC9.19, LED94.1
unnamed: IC9.20, LED93.1
unnamed: IC9.21, LED92.1
unnamed: IC9.22, LED91.1
unnamed: IC9.23, LED90.1
unnamed: IC9.24, LED89.1
unnamed: IC9.25, LED88.1
unnamed: IC9.26, LED87.1
unnamed: IC9.27, LED86.1
unnamed: IC9.28, LED85.1
unnamed: IC9.31, R8.2
unnamed: IC10.15, XA1.D9
unnamed: IC6.3, IC7.3, IC8.3, IC9.3, IC11.3, IC12.3, IC14.3, IC15.3, XA1.D5
unnamed: IC8.29, IC11.4
unnamed: IC11.5, LED97.1
unnamed: IC11.6, LED98.1
unnamed: IC11.7, LED99.1
unnamed: IC11.8, LED100.1
unnamed: IC11.9, LED101.1
unnamed: IC11.10, LED102.1
unnamed: IC11.11, LED103.1
unnamed: IC11.12, LED104.1
unnamed: IC11.13, LED105.1
unnamed: IC11.14, LED106.1
unnamed: IC11.15, LED107.1
unnamed: IC11.16, LED108.1
unnamed: IC11.17, LED132.1
unnamed: IC11.18, LED131.1
unnamed: IC11.19, LED130.1
unnamed: IC11.20, LED129.1
unnamed: IC11.21, LED128.1
unnamed: IC11.22, LED127.1
unnamed: IC11.23, LED126.1
unnamed: IC11.24, LED125.1
unnamed: IC11.25, LED124.1
unnamed: IC11.26, LED123.1
unnamed: IC11.27, LED122.1
unnamed: IC11.28, LED121.1
unnamed: IC11.29, IC14.4
unnamed: IC6.30, IC7.30, IC8.30, IC9.30, IC11.30, IC12.30, IC14.30, IC15.30, XA1.D4
unnamed: IC11.31, R9.2
unnamed: IC9.29, IC12.4
unnamed: IC12.5, LED109.1
unnamed: IC12.6, LED110.1
unnamed: IC12.7, LED111.1
unnamed: IC12.8, LED112.1
unnamed: IC12.9, LED113.1
unnamed: IC12.10, LED114.1
unnamed: IC12.11, LED115.1
unnamed: IC12.12, LED116.1
unnamed: IC12.13, LED117.1
unnamed: IC12.14, LED118.1
unnamed: IC12.15, LED119.1
unnamed: IC12.16, LED120.1
unnamed: IC12.17, LED144.1
unnamed: IC12.18, LED143.1
unnamed: IC12.19, LED142.1
unnamed: IC12.20, LED141.1
unnamed: IC12.21, LED140.1
unnamed: IC12.22, LED139.1
unnamed: IC12.23, LED138.1
unnamed: IC12.24, LED137.1
unnamed: IC12.25, LED136.1
unnamed: IC12.26, LED135.1
unnamed: IC12.27, LED134.1
unnamed: IC12.28, LED133.1
unnamed: IC12.29, IC15.4
unnamed: IC12.31, R10.2
unnamed: IC13.15, XA1.D10
unnamed: IC14.5, LED145.1
unnamed: IC14.6, LED146.1
unnamed: IC14.7, LED147.1
unnamed: IC14.8, LED148.1
unnamed: IC14.9, LED149.1
unnamed: IC14.10, LED150.1
unnamed: IC14.11, LED151.1
unnamed: IC14.12, LED152.1
unnamed: IC14.13, LED153.1
unnamed: IC14.14, LED154.1
unnamed: IC14.15, LED155.1
unnamed: IC14.16, LED156.1
unnamed: IC14.17, LED180.1
unnamed: IC14.18, LED179.1
unnamed: IC14.19, LED178.1
unnamed: IC14.20, LED177.1
unnamed: IC14.21, LED176.1
unnamed: IC14.22, LED175.1
unnamed: IC14.23, LED174.1
unnamed: IC14.24, LED173.1
unnamed: IC14.25, LED172.1
unnamed: IC14.26, LED171.1
unnamed: IC14.27, LED170.1
unnamed: IC14.28, LED169.1
unnamed: IC6.4, IC14.29
unnamed: IC14.31, R11.2
unnamed: IC15.5, LED157.1
unnamed: IC15.6, LED158.1
unnamed: IC15.7, LED159.1
unnamed: IC15.8, LED160.1
unnamed: IC15.9, LED161.1
unnamed: IC15.10, LED162.1
unnamed: IC15.11, LED163.1
unnamed: IC15.12, LED164.1
unnamed: IC15.13, LED165.1
unnamed: IC15.14, LED166.1
unnamed: IC15.15, LED167.1
unnamed: IC15.16, LED168.1
unnamed: IC15.17, LED192.1
unnamed: IC15.18, LED191.1
unnamed: IC15.19, LED190.1
unnamed: IC15.20, LED189.1
unnamed: IC15.21, LED188.1
unnamed: IC15.22, LED187.1
unnamed: IC15.23, LED186.1
unnamed: IC15.24, LED185.1
unnamed: IC15.25, LED184.1
unnamed: IC15.26, LED183.1
unnamed: IC15.27, LED182.1
unnamed: IC15.28, LED181.1
unnamed: IC15.31, R12.2
unnamed: IC16.15, XA1.D11
unnamed: IC17.15, XA1.D12
unnamed: J2.3, S3.1
unnamed: R1.1, S1.3
unnamed: R2.1, S1.1

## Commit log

2021-10-18 Creating first repository description
2021-10-18 Update LICENSE
2021-10-18 Rename OptoPlate_topPlate.ino to OptoPlate_topArduino.ino
2021-10-18 Rename PlateReader_bottomPlate.ino to PlateReader_bottomArduino.ino
2021-10-20 Rename createFit1.m to FirstFit.m
